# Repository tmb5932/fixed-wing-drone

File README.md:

# Autonomous RC Plane

A custom flight controller for a fixed-wing RC plane, built from scratch, both the PCB and the firmware. It's built around an ESP32-S3 and runs in-between a standard RC receiver and the servos/esc, giving the plane an onboard brain capable of taking over from the pilot and flying autonomously.

All software is written in ESP-IDF (specifically v5.5). It's a personal challenge to write as much of it as possible without plug-and-play libraries (ESP-IDF's own UART/I2C drivers are fair game), mainly the device drivers and the flight control logic.

## The Goal

The flight control system is a cascade of PID loops: GPS waypoint/heading navigation on the outside, commanding roll/pitch attitude loops on the inside, plus an airspeed loop on the throttle. Target milestones, roughly in order:

- [x] RC pass-through with working sensor drivers (IMU, GPS) and RC I/O
- [x] First flight (manual pass-through, October 3, 2026)
- [ ] Stable autonomous level flight
- [ ] Altitude hold
- [ ] GPS-guided heading / waypoint following (implemented and SITL-tested, not flown yet)
- [ ] Autonomous takeoff and landing

Longer term, the hopes are giving it mission-oriented capabilities like payload release or coordinated flight with a second drone.

## Current Status

The plane had its first flight on October 3, 2026, in manual pass-through mode only. The RC link had signal dropouts during that flight, so that's being debugged before anything autonomous is tried in the air. Since then the firmware has gained an on-board flight event log, a longer signal-loss window, and safer behaviour when the radio drops (see Safety below).

Autonomous mode (attitude stabilization, waypoint following, return-to-home) has only been tested on the bench and in the SITL simulator. The roll/pitch/heading gains come from SITL sweeps and still need real flight tuning.

## Hardware

- ESP32-S3
- ICM-20948 IMU (I2C), roll/pitch/yaw via a Madgwick filter, with its AK09916 magnetometer used for compass heading
- GPS module (UART, NMEA)
- MS4525DO differential-pressure airspeed sensor (I2C)
- Standard PWM RC receiver and servos/ESC, running alongside the ESP32 instead of being replaced by it

Future hardware will hopefully include lidar and a barometer.

### PCB

The firmware currently runs on the **v2.1** board: a custom carrier PCB that an ESP32-S3-DevKitC plugs into. Everything plugs into labeled connectors on the board rather than bare GPIO pins:

- 6 RC receiver inputs (PWM), 6 labeled servo outputs, and primary/secondary ESC signal outputs
- Separate UBEC power inputs for the flight controller and the ESC/servo rail, each with P-FET reverse-polarity protection
- JST-SH (STEMMA QT) connectors for the IMU, the barometer, and a spare QT port for future I2C sensors
- A JST-GH connector for the airspeed sensor, a header for the GPS UART, and connectors for a LIDAR
- An accessory I/O header for things like LEDs, a payload-release servo/relay, etc.
    -   (obviously will require alterations to code, but software is easier to change than hardware is...)

The GPIO-to-connector mapping the firmware uses (CH1_OUT_GPIO etc. in main.c) is defined by the board's pinout, not repeated here.

The KiCad sources in [`kicad/`](kicad) are the **next** revisions, which the firmware hasn't been ported to yet:

- [`kicad/flight-controller/`](kicad/flight-controller): flight controller v3.1, a fully integrated 4-layer board (ESP32-S3 module, ICM-42688-P + BMI088 IMUs, DPS368 barometer, microSD, SBUS/CRSF receiver input, USB-C). Pinout and power details are in [`docs/buses.md`](docs/buses.md), and its design review is in [`kicad/flight-controller/design-review-fixed-wing-drone.md`](kicad/flight-controller/design-review-fixed-wing-drone.md).
- [`kicad/mission-board/`](kicad/mission-board): a second ESP32-S3 payload board (camera, motor drivers, switched outputs, servo driver) that talks to the flight controller over UART.
- [`kicad/uwb-radio-kicad/`](kicad/uwb-radio-kicad): a DWM3000 ultra-wideband radio module for ranging between drones.

## Software Architecture

- **RC input:** 6 channels read via the ESP32-S3's MCPWM capture timers. Interrupt-driven edge timestamping converts rising/falling edges into pulse widths directly, no external library.
- **RC/servo output:** 6 servo channels plus 2 dedicated ESC channels, driven via MCPWM comparators on a 20ms timebase. Input/output channel mapping, per-channel PWM range and reversal are all configurable at runtime.
- **IMU:** ICM-20948 and its AK09916 magnetometer driven with hand-written I2C register reads/writes, fused through a ported Madgwick AHRS filter for roll/pitch/yaw, with a stillness-gated gyro bias calibration at boot.
- **GPS:** UART driver with a hand-written NMEA RMC sentence parser, plus u-blox config commands to quiet down unused sentence types and set a 5Hz fix rate.
- **Airspeed:** MS4525DO driver with a boot-time zero-offset calibration and a low-pass filter on the pressure reading.
- **PID:** a small PID module with integral anti-windup, used for roll, pitch, heading and airspeed.
- **Navigation:** a 10Hz task that steers toward GPS waypoints (or holds the heading the plane had when autonomous engaged) by commanding a bank angle, using the compass heading or, when moving, GPS course over ground.
- **Control loop:** a 100Hz task that reads all RC channels every cycle and switches between manual pass-through and autonomous output based on the mode switch (below 1500us = autonomous), RC signal health and sensor availability.

### Safety

- Autonomous mode is only armed after the mode switch has been seen in manual at least once since boot, and it needs a fresh GPS fix to engage.
- If the RC signal is lost for 1 second, the plane returns to its home point (averaged from GPS at power-on), then spirals down with the motor off. With no GPS fix or no home, it spirals down where it is. If autonomous isn't available at all, it holds the surfaces at trim with the motor off instead of replaying the last stick input.
- After a reboot in the air, manual pass-through comes back first, before anything slow in boot.
- A small flight event log in RTC memory records RC dropouts, signal losses, failsafe transitions and the reset reason of every boot. It survives a reset (not a power cycle) and can be read from setup mode after landing.

### SITL

[`sitl/`](sitl) holds host-side simulators that compile the firmware's own `pid.c` and `gps_math.c` against a simple airframe model, used to tune the attitude and heading gains, with an 80-scenario regression suite. See [`sitl/README.md`](sitl/README.md).

## Build / Flash

Set up ESP-IDF v5.5, then from the project root:

```sh
idf.py build
idf.py flash monitor
```

### Setup mode

Holding the board's BOOT button within 5 seconds of power-on boots into a
setup mode instead of normal flight init: it hosts its own WiFi access point
(`plane-fc-setup` by default) with a local web page for calibrating servo/ESC
PWM ranges and direction, remapping RC/servo channels, capturing trim,
planning the GPS mission, tuning PID gains, setting the airframe mixing mode
and airspeed-hold target, running bench control tests, and reading the flight
event log. Connect to the AP
and browse to `http://192.168.4.1/`. Everything is saved to NVS immediately;
a normal reset (BOOT not held) returns to flight mode with those settings
applied.

## Author

Travis Brown

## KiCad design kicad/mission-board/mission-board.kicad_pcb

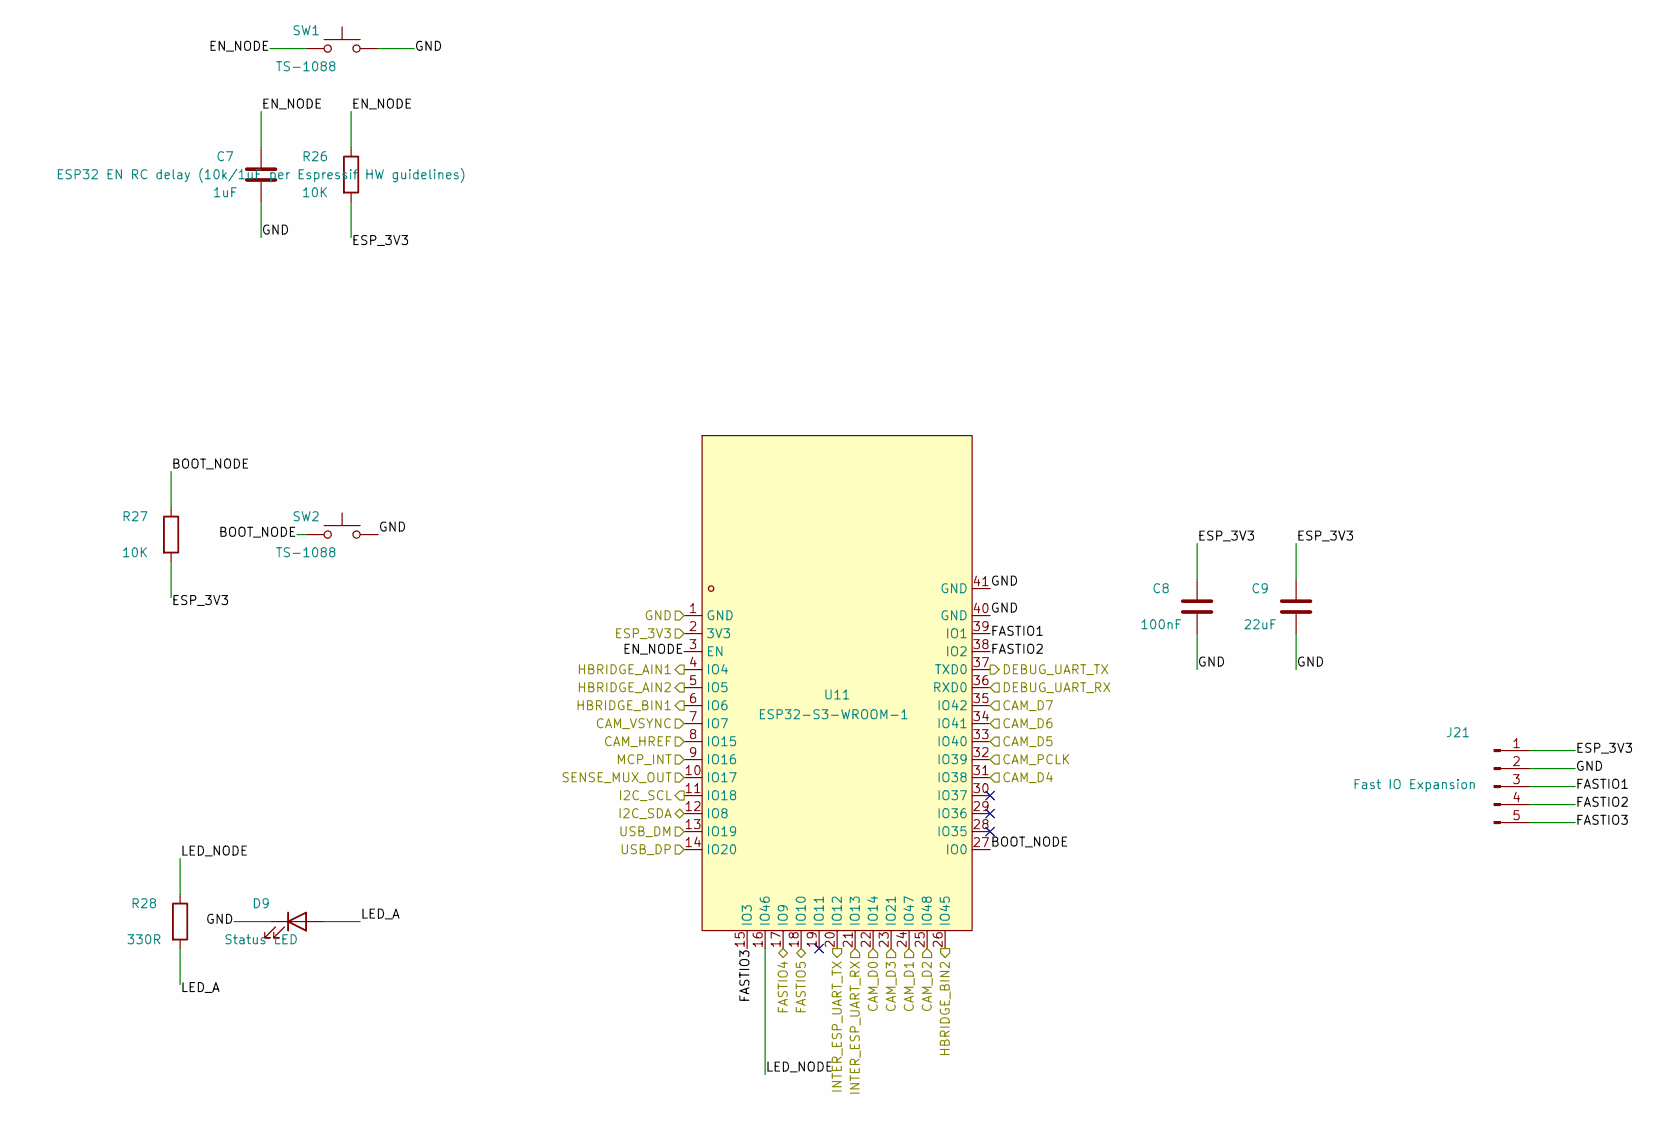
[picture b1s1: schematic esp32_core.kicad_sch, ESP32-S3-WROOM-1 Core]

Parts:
C7: 1uF; C_0402_1005Metric; LCSC Part C52923
C8: 100nF; C_0402_1005Metric; LCSC Part C1525
C9: 22uF; C_0805_2012Metric; LCSC Part C45783
D9: Status LED; LED_0603_1608Metric; LCSC Part C2286
J21: Fast IO Expansion; PinHeader_1x05_P2.54mm_Vertical; LCSC Part C2895846
R26, R27: 10K; R_0402_1005Metric; LCSC Part C25744
R28: 330R; R_0402_1005Metric; LCSC Part C25104
SW1, SW2: TS-1088; SW_SPST_TS-1088-xR020; LCSC Part C720477
U11: ESP32-S3-WROOM-1; WIRELM-SMD_ESP32-S3-WROOM-1; LCSC Part C2913202

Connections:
/CAM_D0: U11.22 (IO14); also elsewhere on the board
/CAM_D1: U11.24 (IO47); also elsewhere on the board
/CAM_D2: U11.25 (IO48); also elsewhere on the board
/CAM_D3: U11.23 (IO21); also elsewhere on the board
/CAM_D4: U11.31 (IO38); also elsewhere on the board
/CAM_D5: U11.33 (IO40); also elsewhere on the board
/CAM_D6: U11.34 (IO41); also elsewhere on the board
/CAM_D7: U11.35 (IO42); also elsewhere on the board
/CAM_HREF: U11.8 (IO15); also elsewhere on the board
/CAM_PCLK: U11.32 (IO39); also elsewhere on the board
/CAM_VSYNC: U11.7 (IO7); also elsewhere on the board
/DEBUG_UART_RX: U11.36 (RXD0); also elsewhere on the board
/DEBUG_UART_TX: U11.37 (TXD0); also elsewhere on the board
/ESP_3V3: C8.1, C9.1, J21.1, R26.2, R27.2, U11.2 (3V3); also elsewhere on the board
/FASTIO4: U11.17 (IO9); also elsewhere on the board
/FASTIO5: U11.18 (IO10); also elsewhere on the board
/GND: C7.2, C8.2, C9.2, D9.1 (K), J21.2, SW1.2, SW2.2, U11.1 (GND), U11.40 (GND), U11.41 (GND); also elsewhere on the board
/HBRIDGE_AIN1: U11.4 (IO4); also elsewhere on the board
/HBRIDGE_AIN2: U11.5 (IO5); also elsewhere on the board
/HBRIDGE_BIN1: U11.6 (IO6); also elsewhere on the board
/HBRIDGE_BIN2: U11.26 (IO45); also elsewhere on the board
/I2C_SCL: U11.11 (IO18); also elsewhere on the board
/I2C_SDA: U11.12 (IO8); also elsewhere on the board
/INTER_ESP_UART_RX: U11.21 (IO13); also elsewhere on the board
/INTER_ESP_UART_TX: U11.20 (IO12); also elsewhere on the board
/MCP_INT: U11.9 (IO16); also elsewhere on the board
/SENSE_MUX_OUT: U11.10 (IO17); also elsewhere on the board
/USB_DM: U11.13 (IO19); also elsewhere on the board
/USB_DP: U11.14 (IO20); also elsewhere on the board
/esp32_core/BOOT_NODE: R27.1, SW2.1, U11.27 (IO0)
/esp32_core/EN_NODE: C7.1, R26.1, SW1.1, U11.3 (EN)
/esp32_core/FASTIO1: J21.3, U11.39 (IO1)
/esp32_core/FASTIO2: J21.4, U11.38 (IO2)
/esp32_core/FASTIO3: J21.5, U11.15 (IO3)
/esp32_core/LED_A: D9.2 (A), R28.2
/esp32_core/LED_NODE: R28.1, U11.16 (IO46)

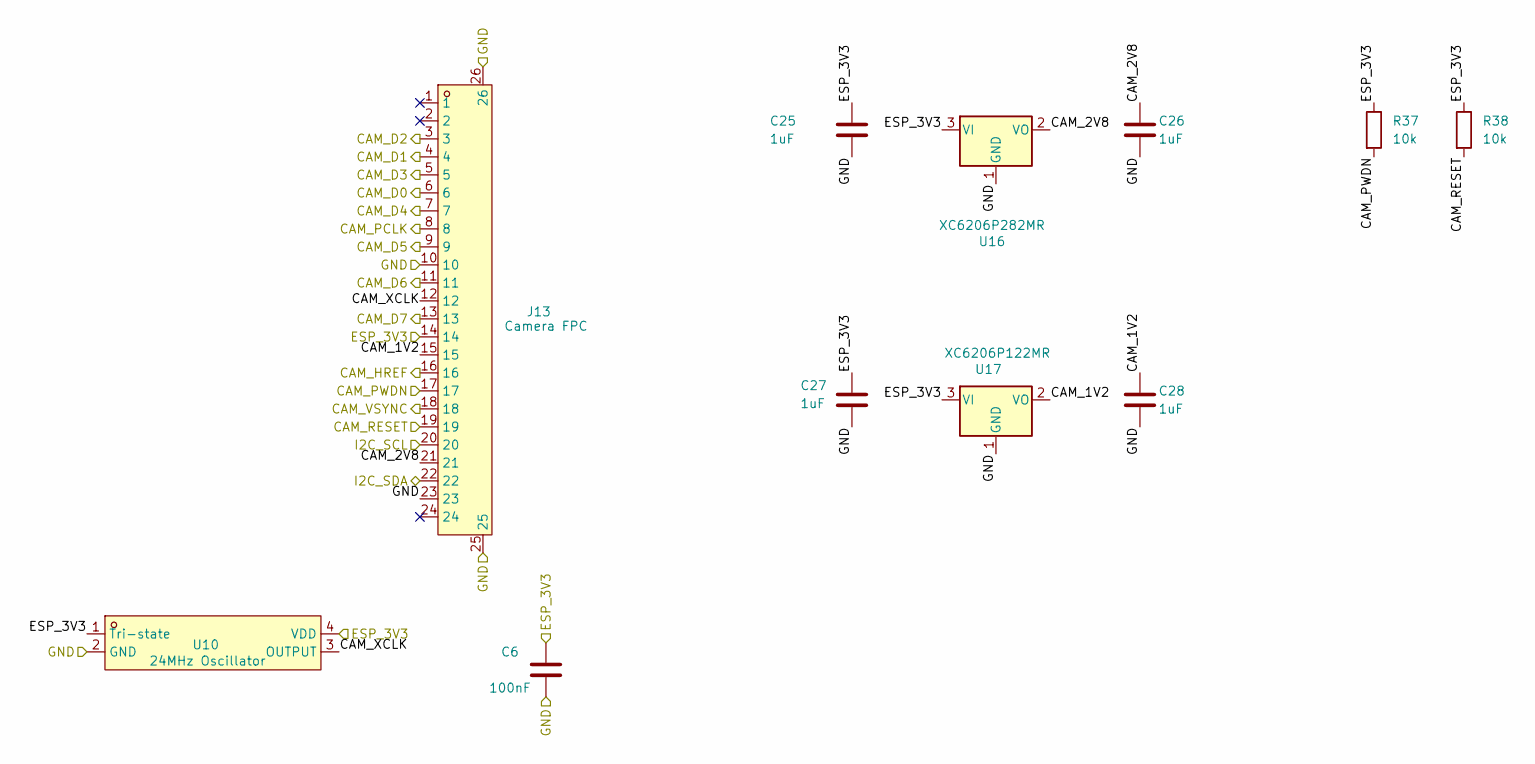
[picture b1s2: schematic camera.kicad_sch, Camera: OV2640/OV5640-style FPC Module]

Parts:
C6: 100nF; C_0402_1005Metric; LCSC Part C1525
C25, C26, C27, C28: 1uF; C_0402_1005Metric; LCSC Part C52923
J13: Camera FPC; FPC-SMD_24P-P0.50_FPC-05F-24PH20; LCSC Part C2856805
R37, R38: 10k; R_0402_1005Metric; LCSC Part C25744
U10: 24MHz Oscillator; OSC-SMD_4P-L3.2-W2.5-BL-1; LCSC Part C717686
U16: XC6206P282MR; SOT-23-3; MPN XC6206P282MR; LCSC Part C5148690
U17: XC6206P122MR; SOT-23-3; MPN XC6206P122MR-Y; LCSC Part C49446785

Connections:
/CAM_D0: J13.6; also elsewhere on the board
/CAM_D1: J13.4; also elsewhere on the board
/CAM_D2: J13.3; also elsewhere on the board
/CAM_D3: J13.5; also elsewhere on the board
/CAM_D4: J13.7; also elsewhere on the board
/CAM_D5: J13.9; also elsewhere on the board
/CAM_D6: J13.11; also elsewhere on the board
/CAM_D7: J13.13; also elsewhere on the board
/CAM_HREF: J13.16; also elsewhere on the board
/CAM_PCLK: J13.8; also elsewhere on the board
/CAM_PWDN: J13.17, R37.2; also elsewhere on the board
/CAM_RESET: J13.19, R38.2; also elsewhere on the board
/CAM_VSYNC: J13.18; also elsewhere on the board
/ESP_3V3: C6.1, C25.1, C27.1, J13.14, R37.1, R38.1, U10.1 (Tri-state), U10.4 (VDD), U16.3 (VI), U17.3 (VI); also elsewhere on the board
/GND: C6.2, C25.2, C26.2, C27.2, C28.2, J13.10, J13.23, J13.25, J13.26, U10.2 (GND), U16.1 (GND), U17.1 (GND); also elsewhere on the board
/I2C_SCL: J13.20; also elsewhere on the board
/I2C_SDA: J13.22; also elsewhere on the board
/camera/CAM_1V2: C28.1, J13.15, U17.2 (VO)
/camera/CAM_2V8: C26.1, J13.21, U16.2 (VO)
/camera/CAM_XCLK: J13.12, U10.3 (OUTPUT)

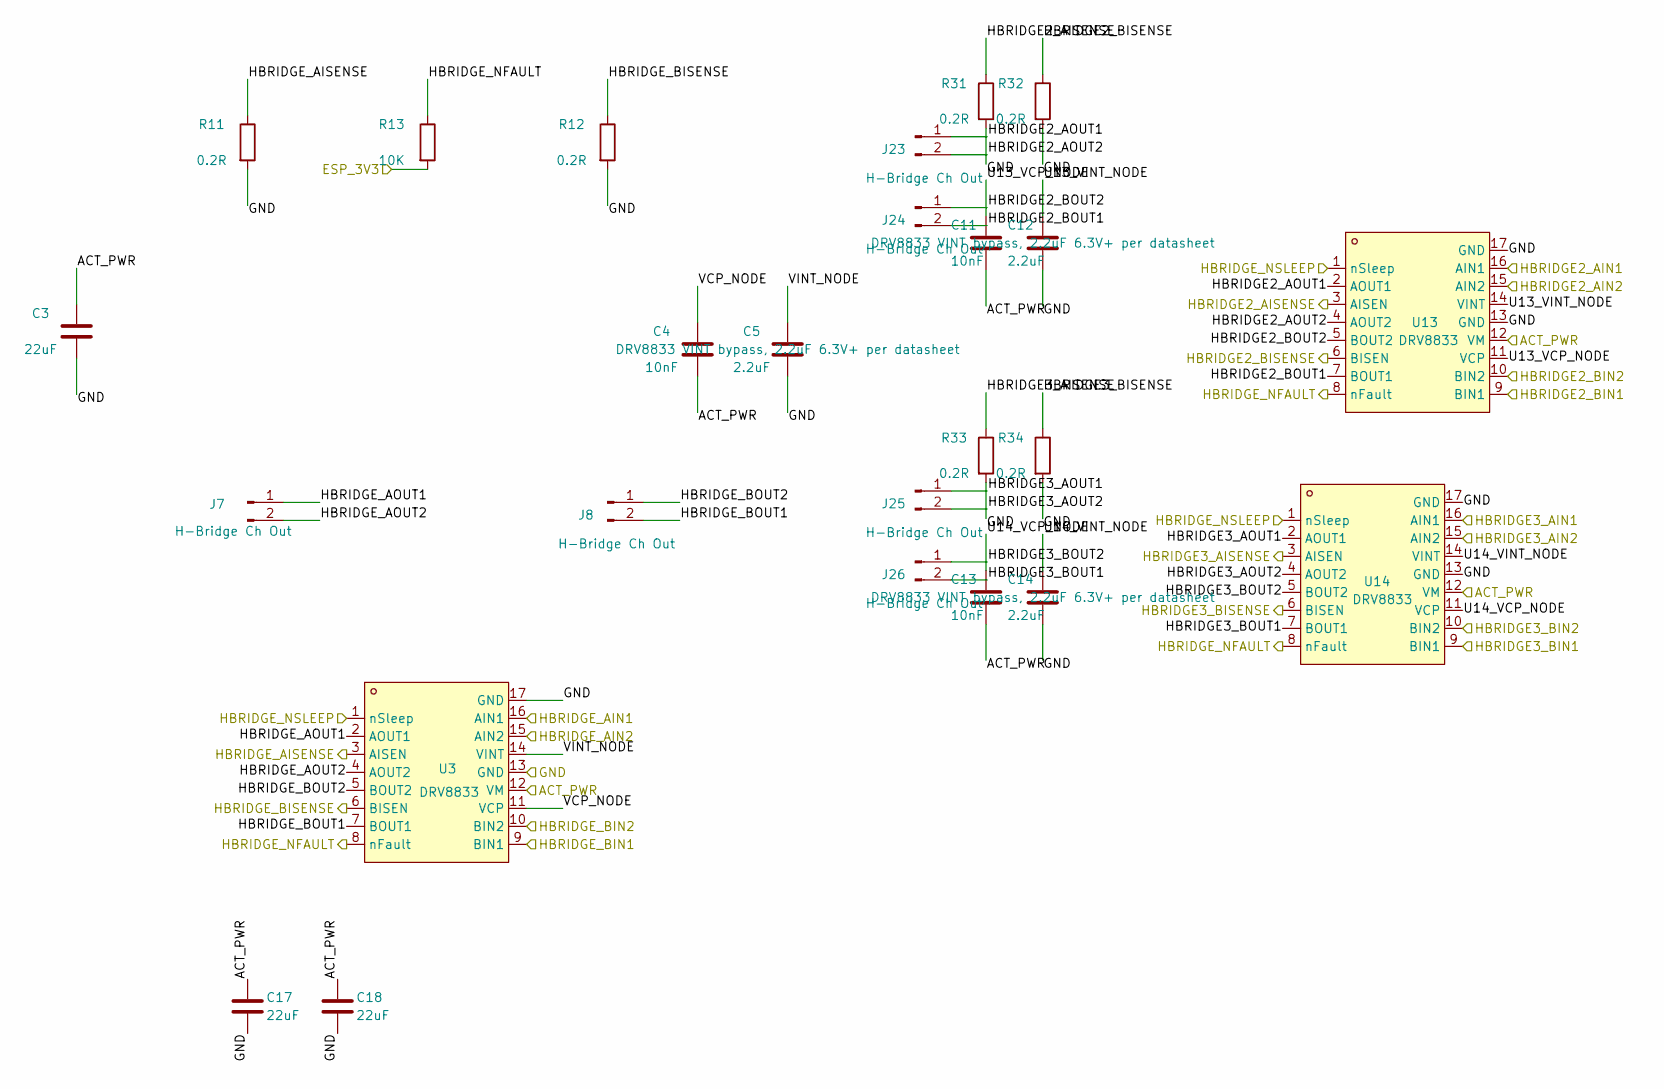
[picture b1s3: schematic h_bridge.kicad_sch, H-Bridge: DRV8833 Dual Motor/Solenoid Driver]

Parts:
C3, C17, C18: 22uF; C_0805_2012Metric; LCSC Part C45783
C4, C11, C13: 10nF; C_0402_1005Metric; LCSC Part C15195
C5, C12, C14: 2.2uF; C_0603_1608Metric; LCSC Part C23630
J7, J8, J23, J24, J25, J26: H-Bridge Ch Out; JST_XH_B2B-XH-A_1x02_P2.50mm_Vertical; LCSC Part C158012
R11, R12, R31, R32, R33, R34: 0.2R; R_1206_3216Metric; LCSC Part C25335
R13: 10K; R_0402_1005Metric; LCSC Part C25744
U3, U13, U14: DRV8833; TSSOP-16_L5.0-W4.4-P0.65-LS6.4-BL-EP; LCSC Part C50506

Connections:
/ACT_PWR: C3.1, C4.2, C11.2, C13.2, C17.1, C18.1, U3.12 (VM), U13.12 (VM), U14.12 (VM); also elsewhere on the board
/ESP_3V3: R13.2; also elsewhere on the board
/GND: C3.2, C5.2, C12.2, C14.2, C17.2, C18.2, R11.2, R12.2, R31.2, R32.2, R33.2, R34.2, U3.13 (GND), U3.17 (GND), U13.13 (GND), U13.17 (GND), U14.13 (GND), U14.17 (GND); also elsewhere on the board
/HBRIDGE2_AIN1: U13.16 (AIN1); also elsewhere on the board
/HBRIDGE2_AIN2: U13.15 (AIN2); also elsewhere on the board
/HBRIDGE2_AISENSE: R31.1, U13.3 (AISEN); also elsewhere on the board
/HBRIDGE2_BIN1: U13.9 (BIN1); also elsewhere on the board
/HBRIDGE2_BIN2: U13.10 (BIN2); also elsewhere on the board
/HBRIDGE2_BISENSE: R32.1, U13.6 (BISEN); also elsewhere on the board
/HBRIDGE3_AIN1: U14.16 (AIN1); also elsewhere on the board
/HBRIDGE3_AIN2: U14.15 (AIN2); also elsewhere on the board
/HBRIDGE3_AISENSE: R33.1, U14.3 (AISEN); also elsewhere on the board
/HBRIDGE3_BIN1: U14.9 (BIN1); also elsewhere on the board
/HBRIDGE3_BIN2: U14.10 (BIN2); also elsewhere on the board
/HBRIDGE3_BISENSE: R34.1, U14.6 (BISEN); also elsewhere on the board
/HBRIDGE_AIN1: U3.16 (AIN1); also elsewhere on the board
/HBRIDGE_AIN2: U3.15 (AIN2); also elsewhere on the board
/HBRIDGE_AISENSE: R11.1, U3.3 (AISEN); also elsewhere on the board
/HBRIDGE_BIN1: U3.9 (BIN1); also elsewhere on the board
/HBRIDGE_BIN2: U3.10 (BIN2); also elsewhere on the board
/HBRIDGE_BISENSE: R12.1, U3.6 (BISEN); also elsewhere on the board
/HBRIDGE_NFAULT: R13.1, U3.8 (nFault), U13.8 (nFault), U14.8 (nFault); also elsewhere on the board
/HBRIDGE_NSLEEP: U3.1 (nSleep), U13.1 (nSleep), U14.1 (nSleep); also elsewhere on the board
/h_bridge/HBRIDGE2_AOUT1: J23.1, U13.2 (AOUT1)
/h_bridge/HBRIDGE2_AOUT2: J23.2, U13.4 (AOUT2)
/h_bridge/HBRIDGE2_BOUT1: J24.2, U13.7 (BOUT1)
/h_bridge/HBRIDGE2_BOUT2: J24.1, U13.5 (BOUT2)
/h_bridge/HBRIDGE3_AOUT1: J25.1, U14.2 (AOUT1)
/h_bridge/HBRIDGE3_AOUT2: J25.2, U14.4 (AOUT2)
/h_bridge/HBRIDGE3_BOUT1: J26.2, U14.7 (BOUT1)
/h_bridge/HBRIDGE3_BOUT2: J26.1, U14.5 (BOUT2)
/h_bridge/HBRIDGE_AOUT1: J7.1, U3.2 (AOUT1)
/h_bridge/HBRIDGE_AOUT2: J7.2, U3.4 (AOUT2)
/h_bridge/HBRIDGE_BOUT1: J8.2, U3.7 (BOUT1)
/h_bridge/HBRIDGE_BOUT2: J8.1, U3.5 (BOUT2)
/h_bridge/U13_VCP_NODE: C11.1, U13.11 (VCP)
/h_bridge/U13_VINT_NODE: C12.1, U13.14 (VINT)
/h_bridge/U14_VCP_NODE: C13.1, U14.11 (VCP)
/h_bridge/U14_VINT_NODE: C14.1, U14.14 (VINT)
/h_bridge/VCP_NODE: C4.1, U3.11 (VCP)
/h_bridge/VINT_NODE: C5.1, U3.14 (VINT)

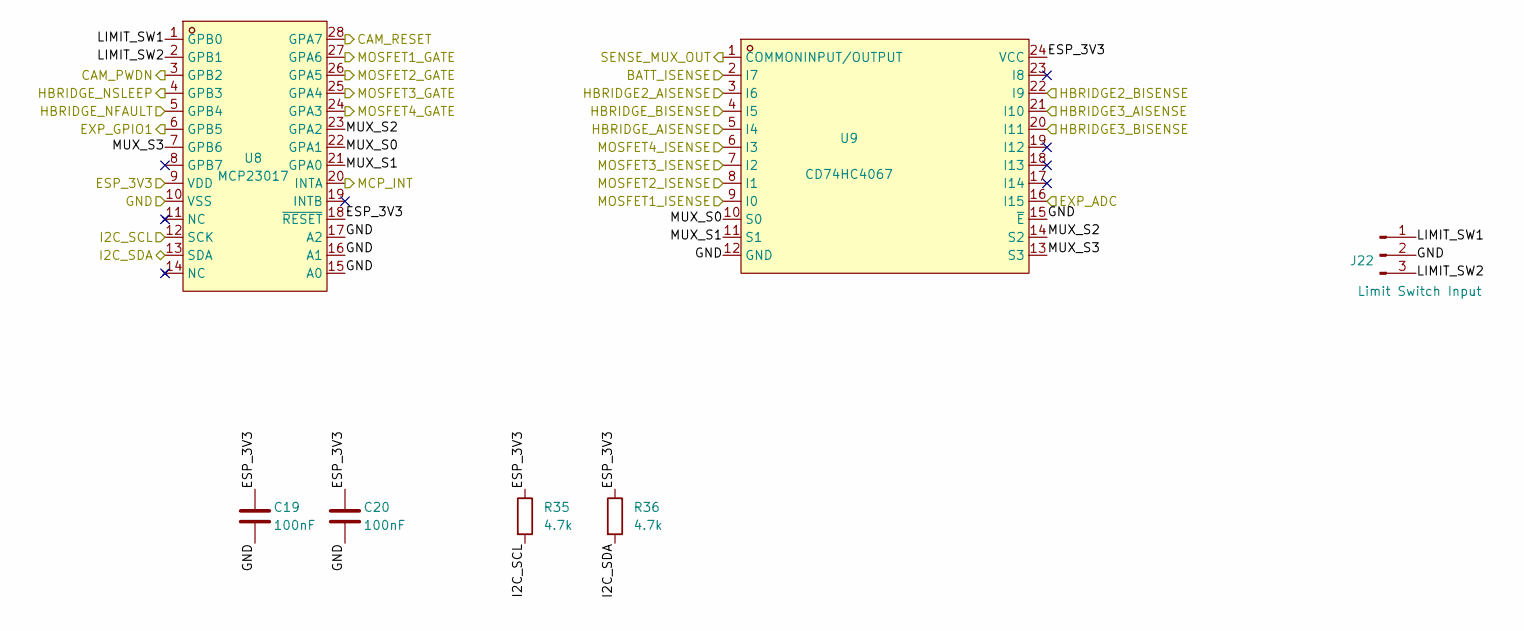
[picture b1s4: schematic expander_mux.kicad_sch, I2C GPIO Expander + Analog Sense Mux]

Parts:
C19, C20: 100nF; C_0402_1005Metric; LCSC Part C1525
J22: Limit Switch Input; JST_XH_B3B-XH-A_1x03_P2.50mm_Vertical; LCSC Part C144394
R35, R36: 4.7k; R_0402_1005Metric; LCSC Part C25900
U8: MCP23017; SOIC-28_L17.9-W7.5-P1.27-LS10.3-BL; LCSC Part C629440
U9: CD74HC4067; SOIC-24_L15.4-W7.5-P1.27-LS10.3-BL; LCSC Part C496123

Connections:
/BATT_ISENSE: U9.2 (I7); also elsewhere on the board
/CAM_PWDN: U8.3 (GPB2); also elsewhere on the board
/CAM_RESET: U8.28 (GPA7); also elsewhere on the board
/ESP_3V3: C19.1, C20.1, R35.1, R36.1, U8.9 (VDD), U8.18 (~RESET), U9.24 (VCC); also elsewhere on the board
/EXP_ADC: U9.16 (I15); also elsewhere on the board
/EXP_GPIO1: U8.6 (GPB5); also elsewhere on the board
/GND: C19.2, C20.2, J22.2, U8.10 (VSS), U8.15 (A0), U8.16 (A1), U8.17 (A2), U9.12 (GND), U9.15 (~E); also elsewhere on the board
/HBRIDGE2_AISENSE: U9.3 (I6); also elsewhere on the board
/HBRIDGE2_BISENSE: U9.22 (I9); also elsewhere on the board
/HBRIDGE3_AISENSE: U9.21 (I10); also elsewhere on the board
/HBRIDGE3_BISENSE: U9.20 (I11); also elsewhere on the board
/HBRIDGE_AISENSE: U9.5 (I4); also elsewhere on the board
/HBRIDGE_BISENSE: U9.4 (I5); also elsewhere on the board
/HBRIDGE_NFAULT: U8.5 (GPB4); also elsewhere on the board
/HBRIDGE_NSLEEP: U8.4 (GPB3); also elsewhere on the board
/I2C_SCL: R35.2, U8.12 (SCK); also elsewhere on the board
/I2C_SDA: R36.2, U8.13 (SDA); also elsewhere on the board
/MCP_INT: U8.20 (INTA); also elsewhere on the board
/MOSFET1_GATE: U8.27 (GPA6); also elsewhere on the board
/MOSFET1_ISENSE: U9.9 (I0); also elsewhere on the board
/MOSFET2_GATE: U8.26 (GPA5); also elsewhere on the board
/MOSFET2_ISENSE: U9.8 (I1); also elsewhere on the board
/MOSFET3_GATE: U8.25 (GPA4); also elsewhere on the board
/MOSFET3_ISENSE: U9.7 (I2); also elsewhere on the board
/MOSFET4_GATE: U8.24 (GPA3); also elsewhere on the board
/MOSFET4_ISENSE: U9.6 (I3); also elsewhere on the board
/SENSE_MUX_OUT: U9.1 (COMMONINPUT/OUTPUT); also elsewhere on the board
/expander_mux/LIMIT_SW1: J22.1, U8.1 (GPB0)
/expander_mux/LIMIT_SW2: J22.3, U8.2 (GPB1)
/expander_mux/MUX_S0: U8.22 (GPA1), U9.10 (S0)
/expander_mux/MUX_S1: U8.21 (GPA0), U9.11 (S1)
/expander_mux/MUX_S2: U8.23 (GPA2), U9.14 (S2)
/expander_mux/MUX_S3: U8.7 (GPB6), U9.13 (S3)

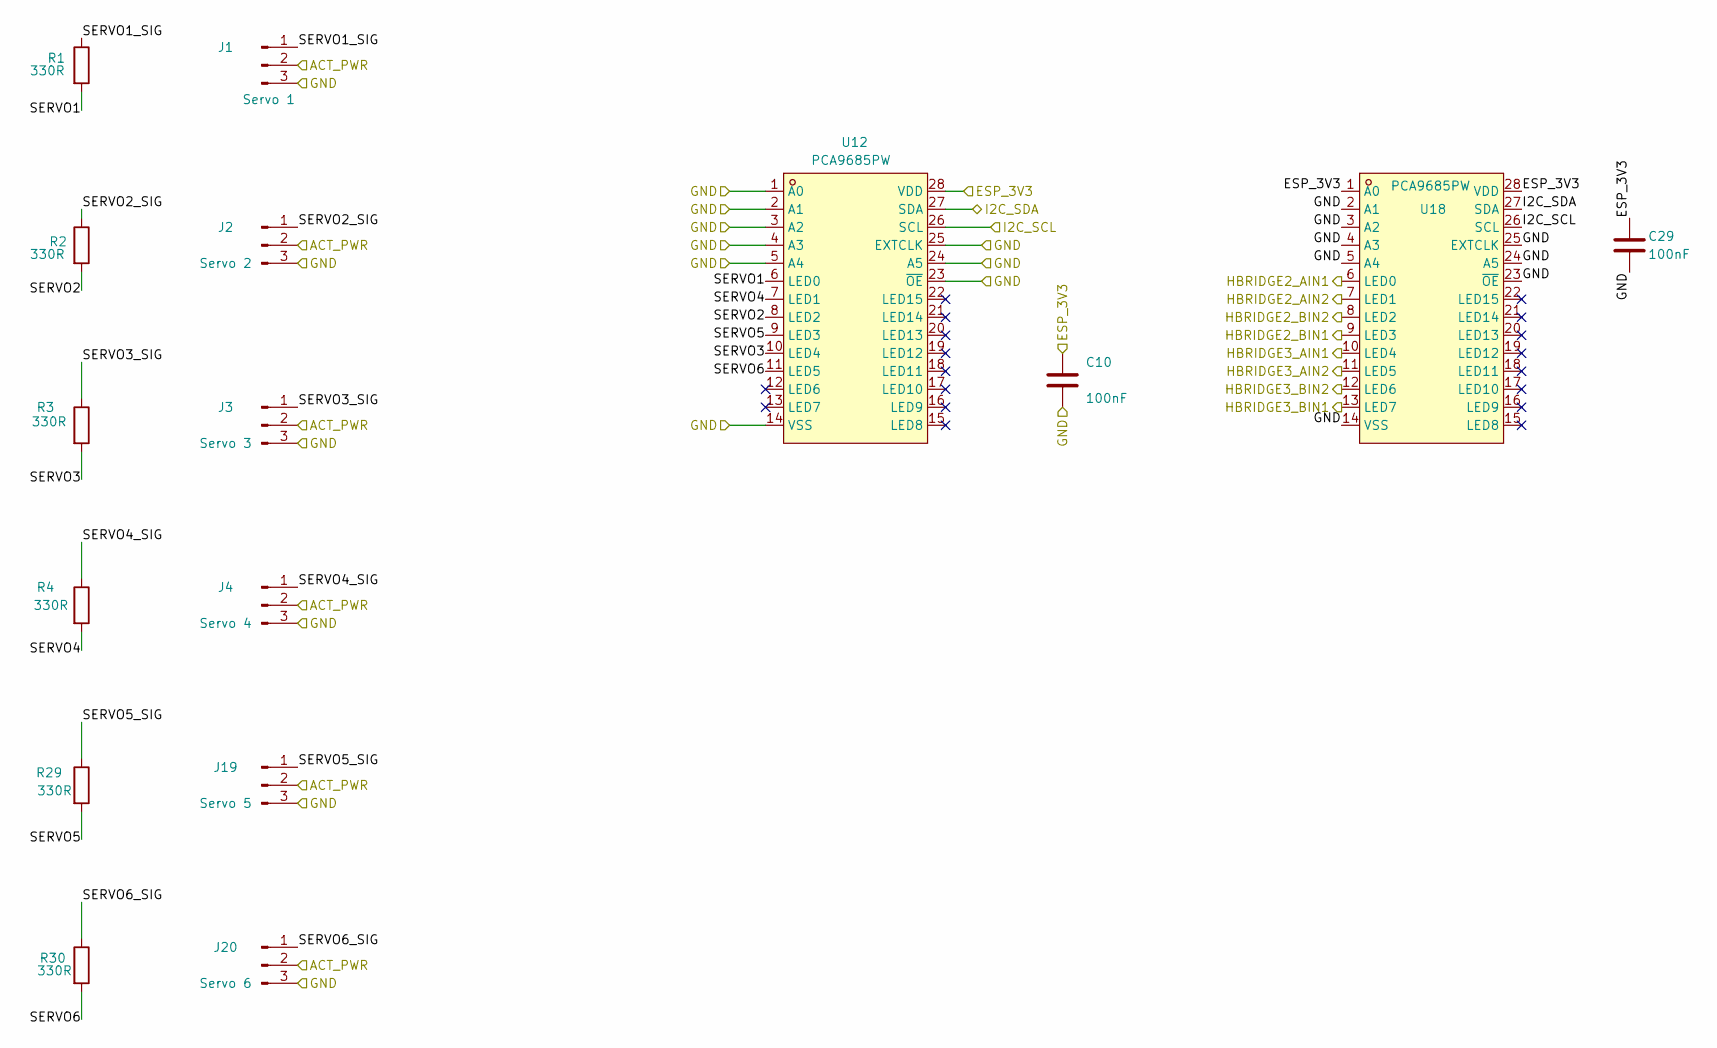
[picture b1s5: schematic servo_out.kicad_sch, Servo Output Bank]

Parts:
C10, C29: 100nF; C_0402_1005Metric; LCSC Part C1525
J1: Servo 1; Molex_KK-254_AE-6410-03A_1x03_P2.54mm_Vertical
J2: Servo 2; Molex_KK-254_AE-6410-03A_1x03_P2.54mm_Vertical
J3: Servo 3; Molex_KK-254_AE-6410-03A_1x03_P2.54mm_Vertical
J4: Servo 4; Molex_KK-254_AE-6410-03A_1x03_P2.54mm_Vertical
J19: Servo 5; Molex_KK-254_AE-6410-03A_1x03_P2.54mm_Vertical
J20: Servo 6; Molex_KK-254_AE-6410-03A_1x03_P2.54mm_Vertical
R1, R2, R3, R4, R29, R30: 330R; R_0402_1005Metric; LCSC Part C25104
U12, U18: PCA9685PW; TSSOP-28_L9.7-W4.4-P0.65-LS6.4-TL; LCSC Part C2678753

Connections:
/ACT_PWR: J1.2, J2.2, J3.2, J4.2, J19.2, J20.2; also elsewhere on the board
/ESP_3V3: C10.1, C29.1, U12.28 (VDD), U18.1 (A0), U18.28 (VDD); also elsewhere on the board
/GND: C10.2, C29.2, J1.3, J2.3, J3.3, J4.3, J19.3, J20.3, U12.1 (A0), U12.2 (A1), U12.3 (A2), U12.4 (A3), U12.5 (A4), U12.14 (VSS), U12.23 (~OE), U12.24 (A5), U12.25 (EXTCLK), U18.2 (A1), U18.3 (A2), U18.4 (A3), U18.5 (A4), U18.14 (VSS), U18.23 (~OE), U18.24 (A5), U18.25 (EXTCLK); also elsewhere on the board
/HBRIDGE2_AIN1: U18.6 (LED0); also elsewhere on the board
/HBRIDGE2_AIN2: U18.7 (LED1); also elsewhere on the board
/HBRIDGE2_BIN1: U18.9 (LED3); also elsewhere on the board
/HBRIDGE2_BIN2: U18.8 (LED2); also elsewhere on the board
/HBRIDGE3_AIN1: U18.10 (LED4); also elsewhere on the board
/HBRIDGE3_AIN2: U18.11 (LED5); also elsewhere on the board
/HBRIDGE3_BIN1: U18.13 (LED7); also elsewhere on the board
/HBRIDGE3_BIN2: U18.12 (LED6); also elsewhere on the board
/I2C_SCL: U12.26 (SCL), U18.26 (SCL); also elsewhere on the board
/I2C_SDA: U12.27 (SDA), U18.27 (SDA); also elsewhere on the board
/servo_out/SERVO1: R1.2, U12.6 (LED0)
/servo_out/SERVO1_SIG: J1.1, R1.1
/servo_out/SERVO2: R2.2, U12.8 (LED2)
/servo_out/SERVO2_SIG: J2.1, R2.1
/servo_out/SERVO3: R3.2, U12.10 (LED4)
/servo_out/SERVO3_SIG: J3.1, R3.1
/servo_out/SERVO4: R4.2, U12.7 (LED1)
/servo_out/SERVO4_SIG: J4.1, R4.1
/servo_out/SERVO5: R29.2, U12.9 (LED3)
/servo_out/SERVO5_SIG: J19.1, R29.1
/servo_out/SERVO6: R30.2, U12.11 (LED5)
/servo_out/SERVO6_SIG: J20.1, R30.1

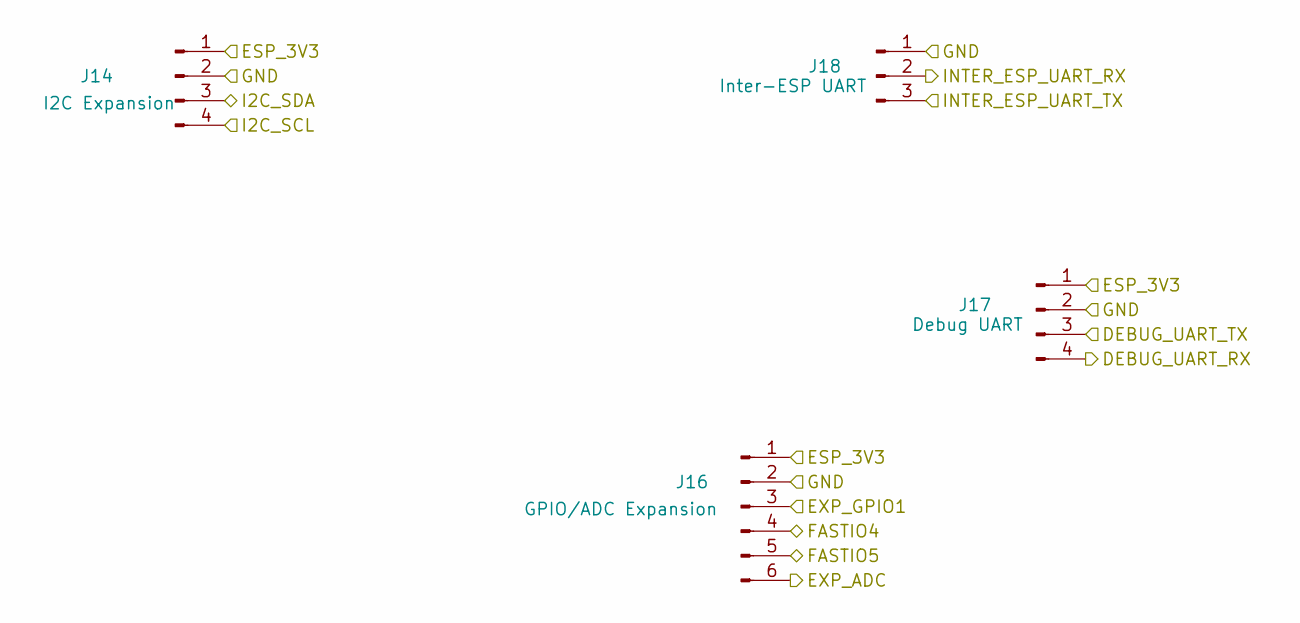
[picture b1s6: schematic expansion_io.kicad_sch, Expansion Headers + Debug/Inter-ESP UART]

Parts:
J14: I2C Expansion; PinHeader_1x04_P2.54mm_Vertical; LCSC Part C2895846
J16: GPIO/ADC Expansion; PinHeader_1x06_P2.54mm_Vertical; LCSC Part C2895846
J17: Debug UART; PinHeader_1x04_P2.54mm_Vertical; LCSC Part C2895846
J18: Inter-ESP UART; JST_GH_BM03B-GHS-TBT_1x03-1MP_P1.25mm_Vertical; LCSC Part C161691

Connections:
/DEBUG_UART_RX: J17.4; also elsewhere on the board
/DEBUG_UART_TX: J17.3; also elsewhere on the board
/ESP_3V3: J14.1, J16.1, J17.1; also elsewhere on the board
/EXP_ADC: J16.6; also elsewhere on the board
/EXP_GPIO1: J16.3; also elsewhere on the board
/FASTIO4: J16.4; also elsewhere on the board
/FASTIO5: J16.5; also elsewhere on the board
/GND: J14.2, J16.2, J17.2, J18.1; also elsewhere on the board
/I2C_SCL: J14.4; also elsewhere on the board
/I2C_SDA: J14.3; also elsewhere on the board
/INTER_ESP_UART_RX: J18.2; also elsewhere on the board
/INTER_ESP_UART_TX: J18.3; also elsewhere on the board

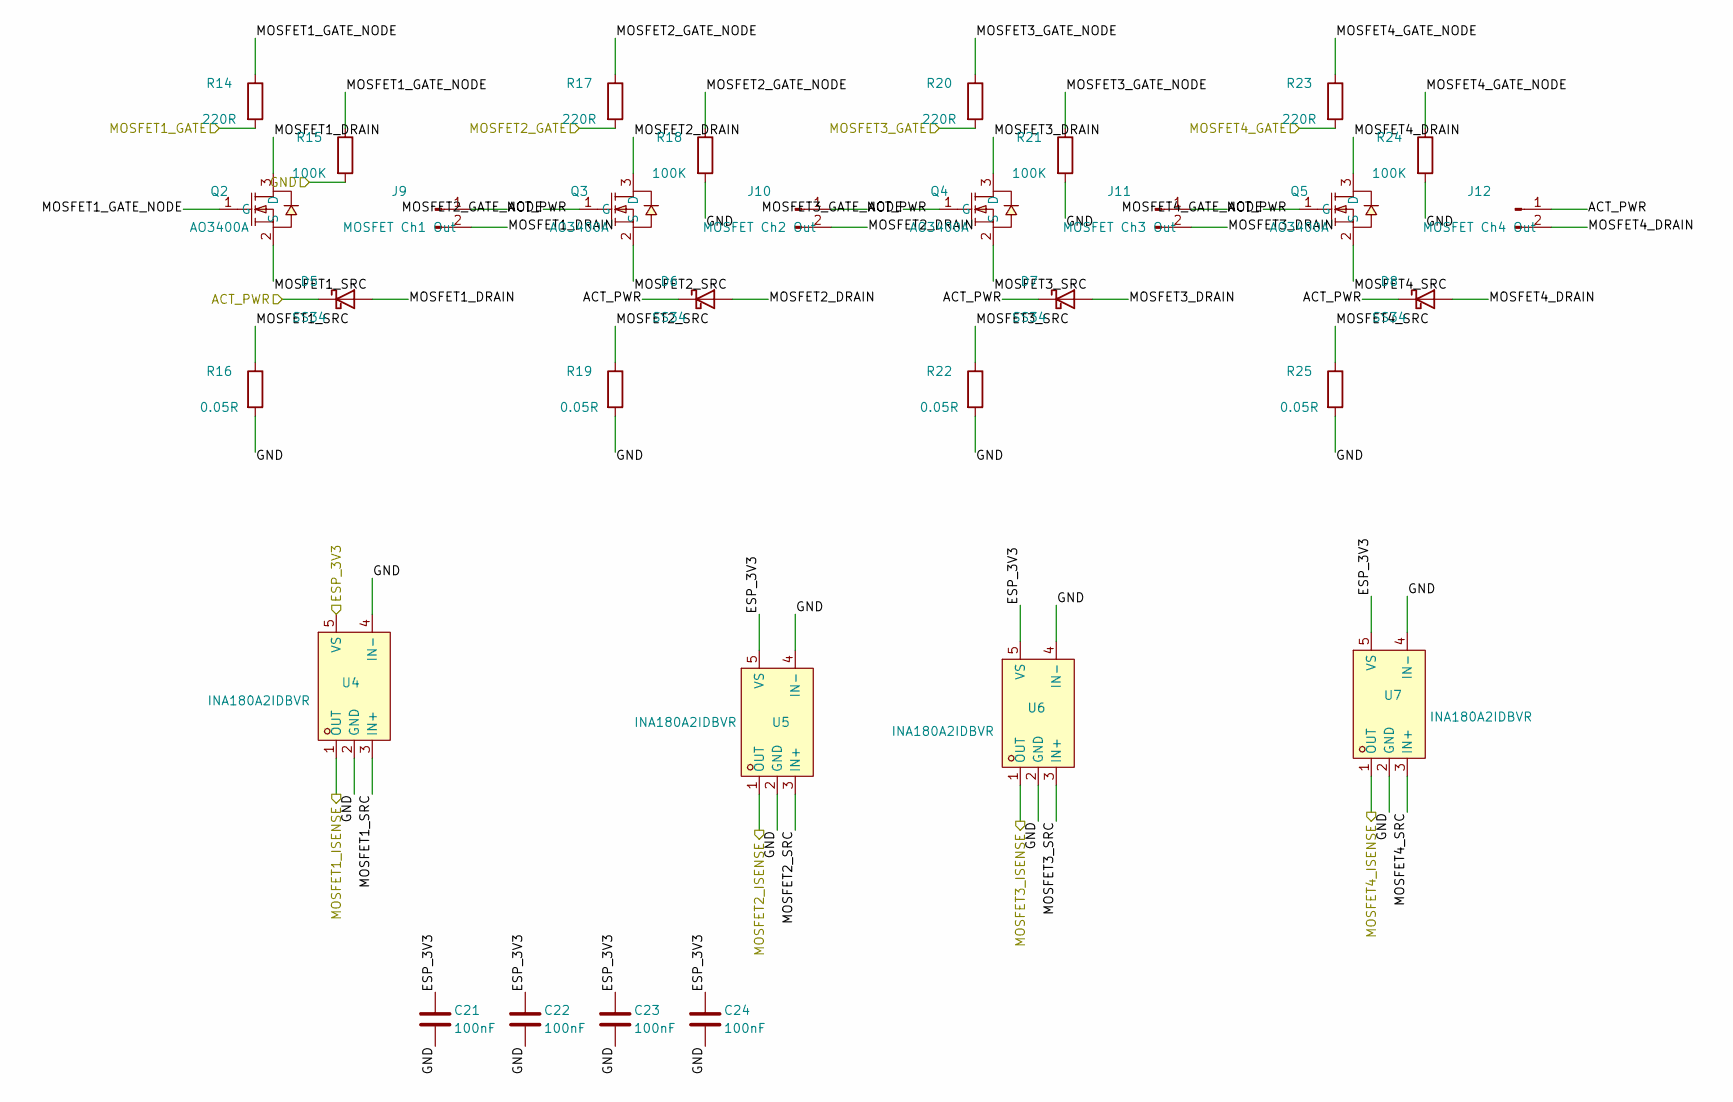
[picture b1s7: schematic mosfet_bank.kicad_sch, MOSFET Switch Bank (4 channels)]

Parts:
C21, C22, C23, C24: 100nF; C_0402_1005Metric; LCSC Part C1525
D5, D6, D7, D8: SS34; D_SMA; LCSC Part C8678
J9: MOSFET Ch1 Out; JST_XH_B2B-XH-A_1x02_P2.50mm_Vertical; LCSC Part C158012
J10: MOSFET Ch2 Out; JST_XH_B2B-XH-A_1x02_P2.50mm_Vertical; LCSC Part C158012
J11: MOSFET Ch3 Out; JST_XH_B2B-XH-A_1x02_P2.50mm_Vertical; LCSC Part C158012
J12: MOSFET Ch4 Out; JST_XH_B2B-XH-A_1x02_P2.50mm_Vertical; LCSC Part C158012
Q2, Q3, Q4, Q5: AO3400A; SOT-23-3_L2.9-W1.3-P1.90-LS2.4-BR; LCSC Part C20917
R14, R17, R20, R23: 220R; R_0402_1005Metric; LCSC Part C25091
R15, R18, R21, R24: 100K; R_0402_1005Metric; LCSC Part C25741
R16, R19, R22, R25: 0.05R; R_1206_3216Metric; LCSC Part C127691
U4, U5, U6, U7: INA180A2IDBVR; SOT-23-5_L3.0-W1.7-P0.95-LS2.8-BL; LCSC Part C192764

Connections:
/ACT_PWR: D5.1 (K), D6.1 (K), D7.1 (K), D8.1 (K), J9.1, J10.1, J11.1, J12.1; also elsewhere on the board
/ESP_3V3: C21.1, C22.1, C23.1, C24.1, U4.5 (VS), U5.5 (VS), U6.5 (VS), U7.5 (VS); also elsewhere on the board
/GND: C21.2, C22.2, C23.2, C24.2, R15.2, R16.2, R18.2, R19.2, R21.2, R22.2, R24.2, R25.2, U4.2 (GND), U4.4 (IN-), U5.2 (GND), U5.4 (IN-), U6.2 (GND), U6.4 (IN-), U7.2 (GND), U7.4 (IN-); also elsewhere on the board
/MOSFET1_GATE: R14.2; also elsewhere on the board
/MOSFET1_ISENSE: U4.1 (OUT); also elsewhere on the board
/MOSFET2_GATE: R17.2; also elsewhere on the board
/MOSFET2_ISENSE: U5.1 (OUT); also elsewhere on the board
/MOSFET3_GATE: R20.2; also elsewhere on the board
/MOSFET3_ISENSE: U6.1 (OUT); also elsewhere on the board
/MOSFET4_GATE: R23.2; also elsewhere on the board
/MOSFET4_ISENSE: U7.1 (OUT); also elsewhere on the board
/mosfet_bank/MOSFET1_DRAIN: D5.2 (A), J9.2, Q2.3 (D)
/mosfet_bank/MOSFET1_GATE_NODE: Q2.1 (G), R14.1, R15.1
/mosfet_bank/MOSFET1_SRC: Q2.2 (S), R16.1, U4.3 (IN+)
/mosfet_bank/MOSFET2_DRAIN: D6.2 (A), J10.2, Q3.3 (D)
/mosfet_bank/MOSFET2_GATE_NODE: Q3.1 (G), R17.1, R18.1
/mosfet_bank/MOSFET2_SRC: Q3.2 (S), R19.1, U5.3 (IN+)
/mosfet_bank/MOSFET3_DRAIN: D7.2 (A), J11.2, Q4.3 (D)
/mosfet_bank/MOSFET3_GATE_NODE: Q4.1 (G), R20.1, R21.1
/mosfet_bank/MOSFET3_SRC: Q4.2 (S), R22.1, U6.3 (IN+)
/mosfet_bank/MOSFET4_DRAIN: D8.2 (A), J12.2, Q5.3 (D)
/mosfet_bank/MOSFET4_GATE_NODE: Q5.1 (G), R23.1, R24.1
/mosfet_bank/MOSFET4_SRC: Q5.2 (S), R25.1, U7.3 (IN+)
